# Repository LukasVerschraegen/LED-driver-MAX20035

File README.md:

# LED-driver-MAX20035
Dit is een schoolproject voor de vakken Industriële toepassing (vermogenelektronica) en Geavanceerd printontwerp.

Enkele video's zijn terug te vinden op mijn youtube kanaal.
https://www.youtube.com/watch?v=1G2xKRNUYQ0&list=PL1lBQKZjCus0v_I9x_oXpihpboHuMBEch

[omschrijving project.pdf](https://github.com/LukasVerschraegen/LED-driver-MAX20035/files/10492971/omschrijving.project.pdf)

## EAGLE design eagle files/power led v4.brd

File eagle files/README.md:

Hier vindt u de files om aanpassingen te maken of voor alles in detail te bekijken.
In de submap, vindt u zowel elke laag apart in pdf als de schema's in pdf vorm.

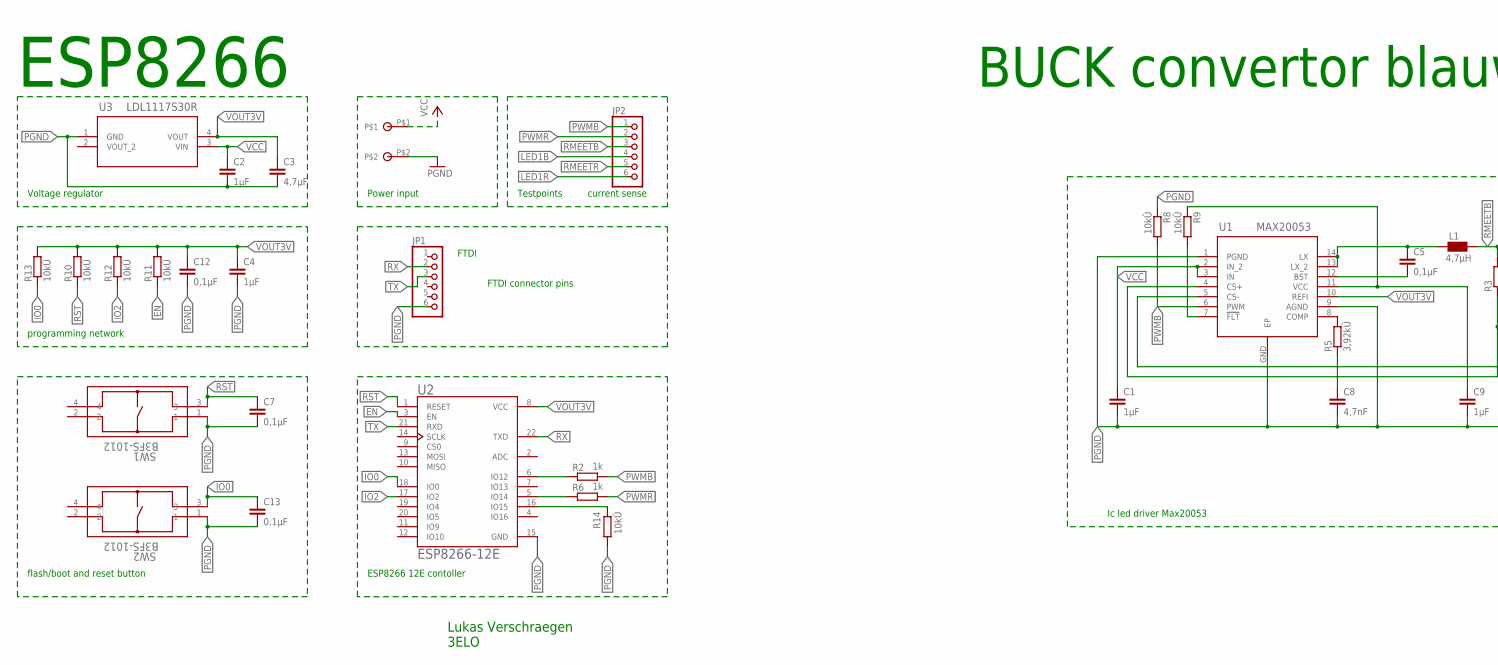
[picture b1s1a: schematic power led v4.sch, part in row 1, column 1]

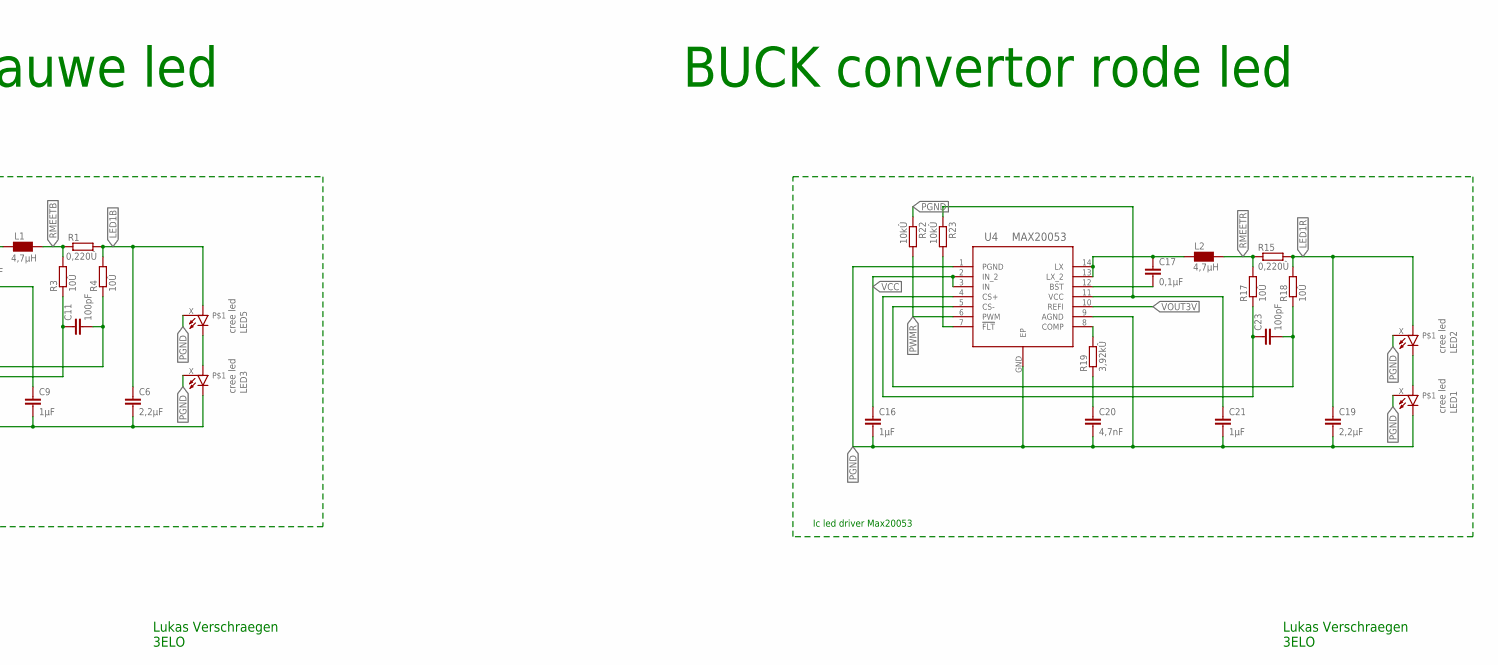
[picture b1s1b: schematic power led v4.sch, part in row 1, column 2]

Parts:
C1, C2, C4, C9, C16, C21: 1µF; C1206
C3: 4,7µF; C1206
C5, C7, C12, C13, C17: 0,1µF; C1206
C6, C19: 2,2µF; C1206
C8, C20: 4,7nF; C1206
C11, C23: 100pF; C1206
JP1, JP2: PINHD-1X6; 1X06
L1, L2: 4,7µH; IND_7447789004_WRE-M
LED1, LED2, LED3, LED5: cree led; CREE_XLAMP
R1, R15: 0,220Û; R1206
R2, R6: 1k; R1206
R3, R4, R17, R18: 10Û; R1206
R5, R19: 3,92kÛ; R1206
R8, R9, R10, R11, R12, R13, R14, R22, R23: 10kÛ; R1206
SW1, SW2: B3FS-1012; SW_B3FS-1010_OMR
U1, U4: MAX20053; 21-0108-E_14L_MXM-M
U2: ESP8266-12E; XCVR_ESP8266-12E/ESP-12E
U3: LDL1117S30R; SOT223_STM
X1: TERMINA5MM; TERMINAL5MM

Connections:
BSTB: C5.2, U1.12 (BST)
BSTR: C17.2, U4.12 (BST)
COMPB: R5.2, U1.8 (COMP)
COMPR: R19.2, U4.8 (COMP)
CS+B: C11.1, R3.1, U1.4 (CS+)
CS+R: C23.1, R17.1, U4.4 (CS+)
CS-B: C11.2, R4.1, U1.5 (CS-)
CS-R: C23.2, R18.1, U4.5 (CS-)
EN: R11.1, U2.3 (EN)
FLTB: R9.2, U1.7 (!FLT)
FLTR: R23.2, U4.7 (!FLT)
IO0: C13.1, R13.1, SW2.3, U2.18 (IO0)
IO2: R12.1, U2.17 (IO2)
IO15: R14.1, U2.16 (IO15)
LED1B: C6.1, JP2.4, LED5.A, LED5.A@1 (A), R1.2, R4.2
LED1R: C19.1, JP2.6, LED2.A, LED2.A@1 (A), R15.2, R18.2
LED2B: LED3.A, LED3.A@1 (A), LED5.C, LED5.C@1 (C)
LED2R1: LED1.A, LED1.A@1 (A), LED2.C, LED2.C@1 (C)
LXB: C5.1, L1.2, U1.13 (LX_2), U1.14 (LX)
LXR: C17.1, L2.2, U4.13 (LX_2), U4.14 (LX)
unnamed: C20.1, R19.1
unnamed: C8.1, R5.1
unnamed: R2.1, U2.6 (IO12)
unnamed: R6.1, U2.5 (IO14)
PGND: C1.2, C2.2, C3.2, C4.2, C6.2, C7.2, C8.2, C9.2, C12.2, C13.2, C16.2, C19.2, C20.2, C21.2, JP1.6, LED1.C, LED1.C@1 (C), LED1.X, LED2.X, LED3.C, LED3.C@1 (C), LED3.X, LED5.X, R8.1, R14.2, R22.1, SW1.1, SW2.1, U1.1 (PGND), U1.9 (AGND), U1.GND (EP), U2.15 (GND), U3.1 (GND), U4.1 (PGND), U4.9 (AGND), U4.GND (EP), X1.P$2
PWMB: JP2.1, R2.2, R8.2, U1.6 (PWM)
PWMR: JP2.2, R6.2, R22.2, U4.6 (PWM)
RMEETB: JP2.3, L1.1, R1.1, R3.2
RMEETR: JP2.5, L2.1, R15.1, R17.2
RST: C7.1, R10.1, SW1.3, U2.1 (RESET)
RX: JP1.2, U2.22 (TXD)
TX: JP1.3, U2.21 (RXD)
VCC: C1.1, C2.1, C16.1, U1.2 (IN_2), U1.3 (IN), U3.3 (VIN), U4.2 (IN_2), U4.3 (IN), X1.P$1
VCCB: C9.1, R9.1, U1.11 (VCC)
VCCR: C21.1, R23.1, U4.11 (VCC)
VOUT3V: C3.1, C4.1, C12.1, R10.2, R11.2, R12.2, R13.2, U1.10 (REFI), U2.8 (VCC), U3.4 (VOUT), U4.10 (REFI)

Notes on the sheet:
Lukas Verschraegen 3ELO
ESP8266
BUCK convertor blauwe led
FTDI
Ic led driver Max20053
BUCK convertor rode led
Voltage regulator
programming network
flash/boot and reset button
FTDI connector pins
ESP8266 12E contoller
Power input
Testpoints
current sense

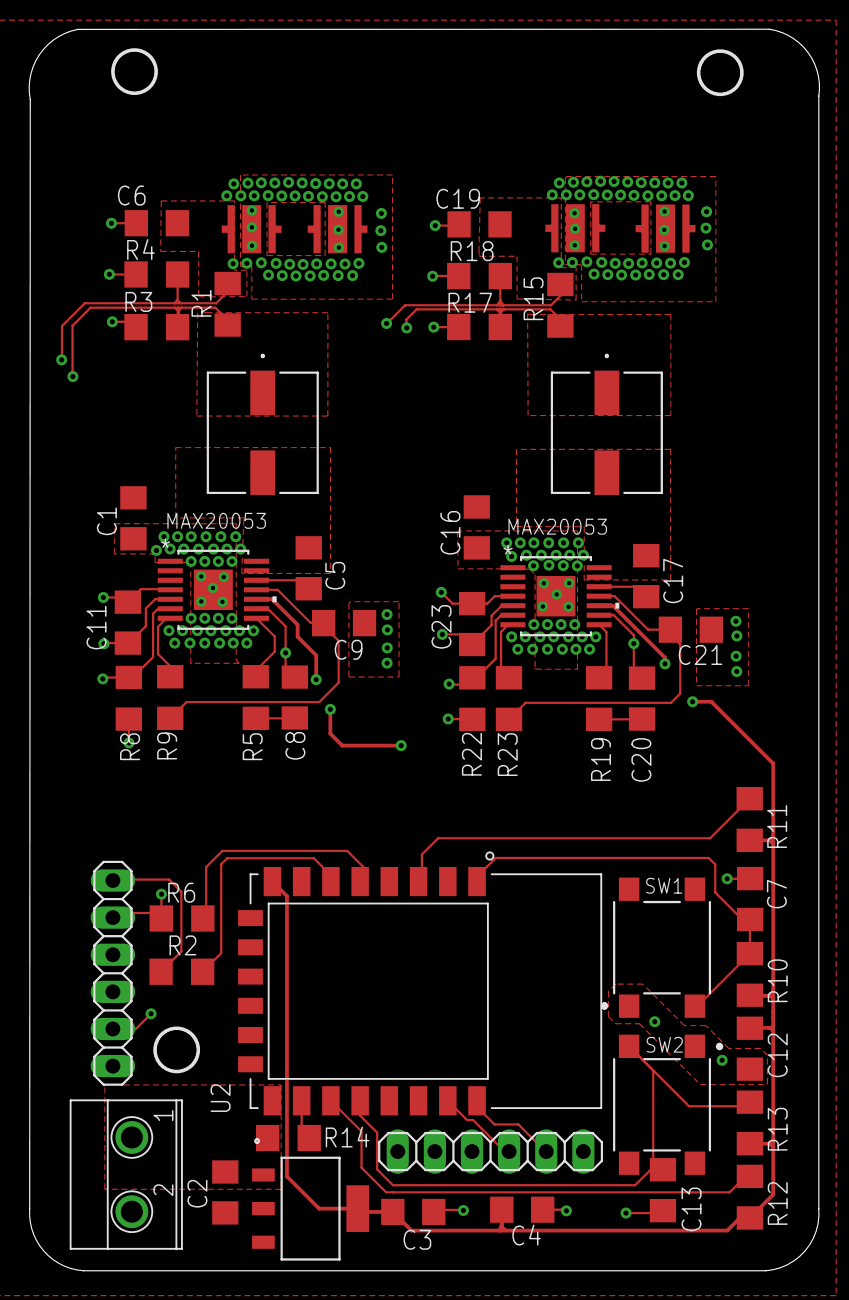
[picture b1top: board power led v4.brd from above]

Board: 4 copper layers, 54.1 x 85.0 mm, 55 parts (0 on the bottom side), 36 nets.

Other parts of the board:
U$1, U$2, U$3: 2,8

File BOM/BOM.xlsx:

| componenten | package | link | aantal | prijs | totaalprijs |  | alternatief aliexpress | prijs
 | MAX20053 | TSSOP | https://be.farnell.com/maxim-integrated-products/max20053aud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 | 2 | 2.58 | 5.16
 | cree led rood | Cree® XLamp® XP-E2 LEDs rood | https://be.farnell.com/cree/xpebrd-l1-0000-00501/led-hb-red-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 | 2 | 1.1399999999999999 | 2.2799999999999998
 | cree led blauw | Cree® XLamp® XP-E2 LEDs blauw | https://be.farnell.com/cree/xpebbl-l1-0000-00301/led-hb-blue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 | 2 | 2.04 | 4.08
 | ldo | LDL1117S30R | https://be.farnell.com/stmicroelectronics/ldl1117s30r/ldo-fi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 | 1 | 1.1599999999999999 | 1.1599999999999999
 | esp8266 | ESP8266-12E | https://opencircuit.be/product/esp8266-esp-12e-wifi-module | 1 | 4.8499999999999996 | 4.8499999999999996 |  | https://nl.aliexpress.com/item/1005001520382593.html?af=3160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 | 1.48
 | knoppen | B3FS-1012 | https://be.farnell.com/omron/b3fs-1012/tactile-switch-0-05a-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 | 2 | 0.89300000000000002 | 1.786
 | pin header 6 pinnen | 1x06 | https://be.farnell.com/amp-te-connectivity/826926-6/header-s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 | 2 | 0.47799999999999998 | 0.95599999999999996
 | terminal block 5mm | 5mm | https://be.farnell.com/camdenboss/ctb1202-2bk/terminal-block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 | 1 | 0.29299999999999998 | 0.29299999999999998
 | spoel 4,7µH | afmetingen afhankelijk van grootte | https://be.farnell.com/wurth-elektronik/7447789004/choke-4-7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 | 2 | 2 | 4
 | condensator 4,7µF | 1206 smd | https://be.farnell.com/kemet/c1206c475k3ractu/cap-4-7-f-25v-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 | 1 | 0.78600000000000003 | 0.78600000000000003
 | condensator 4,7nF | 1206 smd | https://be.farnell.com/kemet/c1206c472k5ractu/cap-4700pf-50v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 | 2 | 0.107 | 0.214
 | condensator 2,2µF | 1206 smd | https://be.farnell.com/avx/12061c225kat2a/cap-2-2-f-100v-10-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 | 2 | 0.36799999999999999 | 0.73599999999999999
 | condensator 1µF | 1206 smd | https://be.farnell.com/avx/12065c105kat2a/cap-1-f-50v-10-x7r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 | 6 | 0.17499999999999999 | 1.0499999999999998
 | condensator 100pF | 1206 smd | https://be.farnell.com/multicomp/mc1206n101j500ct/cap-100pf-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 | 2 | 0.121 | 0.24199999999999999
 | condensator 0,1µF | 1206 smd | https://be.farnell.com/avx/12065c104kat2a/cap-0-1-f-50v-10-x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 | 5 | 7.2999999999999995E-2 | 0.36499999999999999
 | weerstand 0,220Ω | 1206 smd | https://www.digikey.be/nl/products/detail/ohmite/KDV12FR220E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 | 2 | 0.3 | 0.6
 | weerstand 10kΩ | 1206 smd | https://be.farnell.com/bourns/cr1206-fx-1002elf/res-10k-1-0-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 | 9 | 4.6699999999999998E-2 | 0.42030000000000001
 | weerstand 10Ω | 1206 smd | https://be.farnell.com/vishay/crcw120610r0fkeahp/res-10r-1-0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 | 4 | 0.26300000000000001 | 1.052
 | weerstand 1kΩ | 1206 smd | https://be.farnell.com/multicomp/mcwr12x1001ftl/res-1k-1-0-2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 | 2 | 1.38E-2 | 2.76E-2
 | weerstand 3,92kΩ | 1206 smd | https://be.farnell.com/bourns/cr1206-jw-392elf/res-3k9-5-0-2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 | 2 | 4.2000000000000003E-2 | 8.4000000000000005E-2
 |  |  |  |  |  | 30.141900000000003 |  |  | 26.771900000000002

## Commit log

2023-01-24 Create gerber files
2023-01-24 gerberfiles
2023-01-24 Create test

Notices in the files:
parts and their libraries:
COPYRIGHT: Copyright (C) 2018 Accelerated Designs. All rights reserved
COPYRIGHT: Copyright (C) 2022 Ultra Librarian. All rights reserved.
